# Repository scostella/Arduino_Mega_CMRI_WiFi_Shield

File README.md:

# Arduino Mega CMRI WiFi Shield

The **Arduino Mega CMRI WiFi Shield** is a custom expansion board designed to **plug directly into an Arduino Mega 2560**, organizing digital and analog I/O into structured panel‑based connectors while integrating an **ESP8266 ESP‑01** module to provide WiFi connectivity.

When used with the **Arduino CMRI Library**, this shield allows the Arduino Mega to emulate a **CMRI node** supporting both input and output operations over a network connection.

NOTE: It is highly recommended that your JMRI workstation uses a wired connection to the network.  
---

## Overview

The Arduino Mega CMRI WiFi Shield serves as the central interface between an Arduino Mega 2560, auxiliary I/O modules, and a WiFi network. The shield groups Arduino pins into standardized connectors for clean wiring and expansion while enabling wireless CMRI communication via an onboard ESP8266 ESP‑01.

This design is intended for modular CMRI systems where distributed I/O and network connectivity are required.

---

## Key Characteristics

- Plugs directly into an **Arduino Mega 2560**
- Groups digital and analog I/O into **16 sets of 4 pins**
- Compatible with the **Arduino CMRI Library**
- Supports both CMRI **input and output** operations
- Integrated **ESP8266 ESP‑01** socket for WiFi connectivity
- Designed to interface with auxiliary modules in this series
- Passive signal routing (no onboard I/O drivers)

---

## Assembled Board

The image above shows the rendered Arduino Mega CMRI WiFi Shield PCB as it plugs directly into an Arduino Mega 2560.

---

## Board Layout and Function

### Panel Header Grid

Just offset to the **left of the center of the board** is a **4 × 4 grid of 4‑pin headers**.

- Each 4‑pin header represents a **designated panel** in the Arduino Mega CMRI WiFi sketch
- Together, these headers group Arduino digital and analog pins into **16 panel connections**
- The pin groupings map directly to CMRI node definitions in software

This layout is designed to integrate cleanly with the auxiliary modules developed for this system, including those listed in the **Reference Projects** section. The standardized grouping simplifies wiring and ensures consistent mapping between hardware modules and CMRI configuration.

---

### Power Input

On the **left side of the board** is a **single 3‑pin header** supplying:

- **12 V**
- **5 V**
- **Ground**

This header provides power to both the Arduino Mega and the shield, allowing a single power entry point for the CMRI node.

---

### ESP8266 WiFi Integration

The shield includes a **single 2 × 4 socket** for an **ESP8266 ESP‑01** module.

- The ESP‑01 is installed **after programming**
- Once installed, it enables WiFi connectivity for the CMRI node
- Communication between the Arduino Mega and ESP8266 is handled entirely in firmware

This configuration allows the Arduino Mega to communicate with **JMRI or other network‑based CMRI control systems** over WiFi.

---

### Status Indicators

The board includes **two onboard LEDs**:

- **Power LED**  
  Indicates that the Arduino Mega and shield are powered

- **CMRI Connection LED**  
  Indicates when **JMRI or another network‑based CMRI control system** is connected to the emulated CMRI node

These LEDs provide immediate visual feedback on system power and network status.

---

## Intended Use

This shield is well suited for:

- CMRI‑based model railroad layouts
- Distributed CMRI I/O nodes
- Control panels and indicators
- Integration with auxiliary CMRI modules
- WiFi‑enabled CMRI systems using JMRI or similar software

---

## Limited Liability and Disclaimer

This project is provided as an **open‑source hardware design** and is offered **as‑is**, without warranty of any kind.

By using this design, documentation, or any assembled hardware provided by the author, you agree to the following:

- You assume **all responsibility** for proper electrical design, wiring, installation, and use
- The author makes **no guarantees** regarding suitability for any specific application
- The author shall not be held liable for:
  - Damage to equipment
  - Electrical failures
  - Personal injury
  - Property damage
  - Losses resulting from improper use, installation, or modification

Use of this project or any associated hardware constitutes acceptance of these terms.

---

## Availability and Purchase

Fully **assembled and tested** Arduino Mega CMRI WiFi Shield boards are available.

- **Price:** $35 USD per board  
- **Shipping:** Additional, based on destination  
- **Contact:**  
  📧 scostella@seancostella.com  

Please contact the author for current availability, lead times, and shipping details.

---

## Reference Projects

This project integrates with the Arduino CMRI ecosystem. The following projects provide related hardware, firmware, and configuration support:

- **Arduino Mega CMRI WiFi**  
  Arduino sketch for Mega 2560 to operate as CMRI Node with an ESP8266-ESP01 providing WiFi connectivity.
  https://github.com/scostella/Arduino_Mega_CMRI_WiFi

- **ESP8266 WiFi Setup Utility**  
  ESP sketch to program the ESP8266-ESP01 to work with the Arduino Mega 2560 and connection configuration for your WiFi network.
  https://github.com/scostella/ESP8266WiFiSetup

- **KiCad Custom Library**  
  Library containing all project parts in all designs.
  https://github.com/scostella/KiCadLibrary

- **Arduino Mega CMRI WiFi Shield**  
  KiCad design for a shield for the Arduino Mega 2560 facilitating easy integration with the ESP8266-ESP01 and the CMRI modules listed below.
  https://github.com/scostella/Arduino_Mega_CMRI_WiFi_Shield

- **Arduino Accessory Controller**  
  KiCad design for a board to control accessories up to 1 amp.
  https://github.com/scostella/Arduino-Accessory-Controller

- **Arduino IR Sensor Module - 8 Port**  
  KiCad design for a board to use TCRT5000 IR module to sense object presence which can also be used in the Arduino Mega CMRI WiFi module to group sensors to create virtual block detection.
  https://github.com/scostella/Arduino_IR_Sensor_Module_-_8_Port

- **Arduino Tortoise Controller with Feedback - 8 Port**  
  KiCad design for a board to control Circuitron Tortoise Slow Motion Switch machines and provide feedback on switch position either controlled internally by the voltage applied to the tortoise or an external signal.
  https://github.com/scostella/Arduino_Tortoise_Controller_with_Feedback_-_8_Port

- **Arduino Light Controller**  
  KiCad design for a board to control low amperage lighting and other loads (<10ma) using the Arduino's 5V source.
  https://github.com/scostella/Arduino-Light-Controller

These projects may be used together to form a complete CMRI‑controlled lighting and I/O system.

---

## Repository Contents

```text
/
├── 3V3VoltageRegulator.kicad_sch               # 3.3V Regulated Power Module
├── Arduino Mega CMRI WiFi Shield.jpg           # Rendered image of assembled board
├── Arduino Mega CMRI WiFi Shield.kicad_pcb     # KiCad PCB Layout
├── Arduino Mega CMRI WiFi Shield.kicad_prl     # KiCad Project Settings
├── Arduino Mega CMRI WiFi Shield.kicad_pro     # KiCad Project
├── Arduino Mega CMRI WiFi Shield.kicad_sch     # KiCad Schematic
├── ArduinoReset.kicad_sch                      # Arduino Reset module
├── ESP8266ESP01WiFi.kicad_sch                  # ESP8266ESP01WiFi module
├── LogicLevelShifter.kicad_sch                 # 5V-3.3V Logic Level Shift module
└── README.md

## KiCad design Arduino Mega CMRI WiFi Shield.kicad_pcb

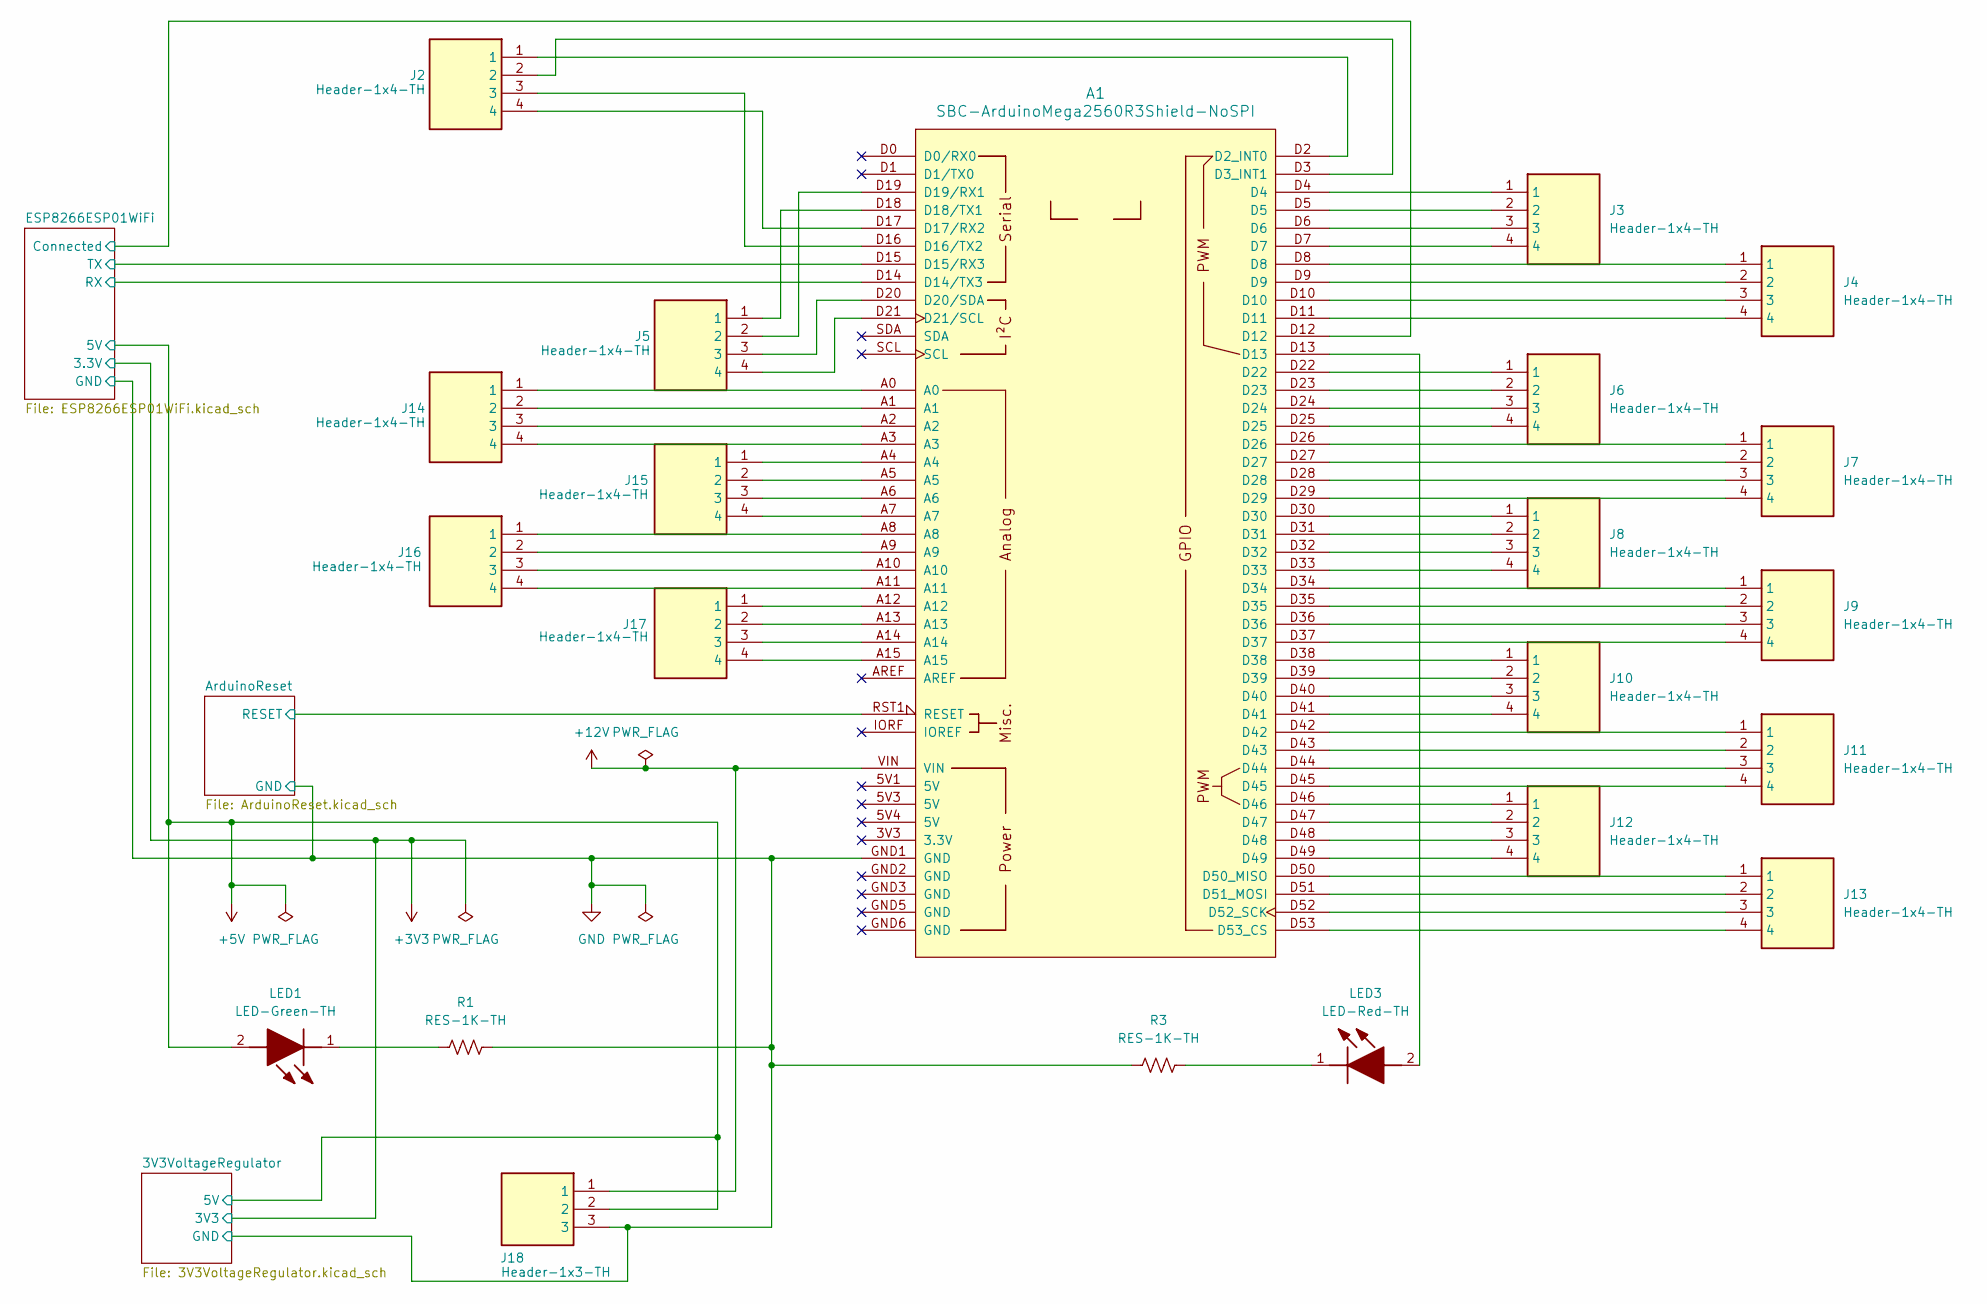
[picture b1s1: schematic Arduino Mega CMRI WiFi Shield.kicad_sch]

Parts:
A1: SBC-ArduinoMega2560R3Shield-NoSPI
J2, J3, J4, J5, J6, J7, J8, J9, J10, J11, J12, J13, J14, J15, J16, J17: Header-1x4-TH; 710-61300411121; Mouser Part Number 710-61300411121
J18: Header-1x3-TH; 710-61300311121; Mouser Part Number 710-61300311121
LED1: LED-Green-TH; 604-WP7113GD; Mouser Part Number 604-WP7113GD
LED3: LED-Red-TH; 604-WP7113ID; Mouser Part Number 604-WP7113ID
R1, R3: RES-1K-TH; R_Axial_DIN0204_L3.6mm_D1.6mm_P7.62mm_Horizontal; Mouser Part Number N/A

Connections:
+5V: J18.2, LED1.2 (A); also elsewhere on the board
+12V: A1.VIN, J18.1
/ArduinoReset/RESET: A1.RST1 (RESET); also elsewhere on the board
/ESP8266ESP01WiFi/Connected: A1.D12; also elsewhere on the board
/ESP8266ESP01WiFi/RX: A1.D14 (D14/TX3); also elsewhere on the board
/ESP8266ESP01WiFi/TX: A1.D15 (D15/RX3); also elsewhere on the board
GND: A1.GND1 (GND), J18.3, R1.2, R3.1; also elsewhere on the board
unnamed: A1.D2 (D2_INT0), J2.1
unnamed: A1.D3 (D3_INT1), J2.2
unnamed: A1.D16 (D16/TX2), J2.3
unnamed: A1.D17 (D17/RX2), J2.4
unnamed: A1.D18 (D18/TX1), J5.1
unnamed: A1.D19 (D19/RX1), J5.2
unnamed: A1.D20 (D20/SDA), J5.3
unnamed: A1.D21 (D21/SCL), J5.4
unnamed: A1.D50 (D50_MISO), J13.1
unnamed: A1.D51 (D51_MOSI), J13.2
unnamed: A1.D52 (D52_SCK), J13.3
unnamed: A1.D53 (D53_CS), J13.4
unnamed: A1.A0, J14.1
unnamed: A1.A1, J14.2
unnamed: A1.A2, J14.3
unnamed: A1.A3, J14.4
unnamed: A1.A4, J15.1
unnamed: A1.A5, J15.2
unnamed: A1.A6, J15.3
unnamed: A1.A7, J15.4
unnamed: A1.A8, J16.1
unnamed: A1.A9, J16.2
unnamed: A1.A10, J16.3
unnamed: A1.A11, J16.4
unnamed: A1.A12, J17.1
unnamed: A1.A13, J17.2
unnamed: A1.A14, J17.3
unnamed: A1.A15, J17.4
unnamed: A1.D4, J3.1
unnamed: A1.D5, J3.2
unnamed: A1.D6, J3.3
unnamed: A1.D7, J3.4
unnamed: A1.D8, J4.1
unnamed: A1.D9, J4.2
unnamed: A1.D10, J4.3
unnamed: A1.D11, J4.4
unnamed: A1.D22, J6.1
unnamed: A1.D23, J6.2
unnamed: A1.D24, J6.3
unnamed: A1.D25, J6.4
unnamed: A1.D26, J7.1
unnamed: A1.D27, J7.2
unnamed: A1.D28, J7.3
unnamed: A1.D29, J7.4
unnamed: A1.D30, J8.1
unnamed: A1.D31, J8.2
unnamed: A1.D32, J8.3
unnamed: A1.D33, J8.4
unnamed: A1.D34, J9.1
unnamed: A1.D35, J9.2
unnamed: A1.D36, J9.3
unnamed: A1.D37, J9.4
unnamed: A1.D38, J10.1
unnamed: A1.D39, J10.2
unnamed: A1.D40, J10.3
unnamed: A1.D41, J10.4
unnamed: A1.D42, J11.1
unnamed: A1.D43, J11.2
unnamed: A1.D44, J11.3
unnamed: A1.D45, J11.4
unnamed: A1.D46, J12.1
unnamed: A1.D47, J12.2
unnamed: A1.D48, J12.3
unnamed: A1.D49, J12.4
unnamed: LED1.1 (K), R1.1
unnamed: A1.D13, LED3.2 (A)
unnamed: LED3.1 (K), R3.2

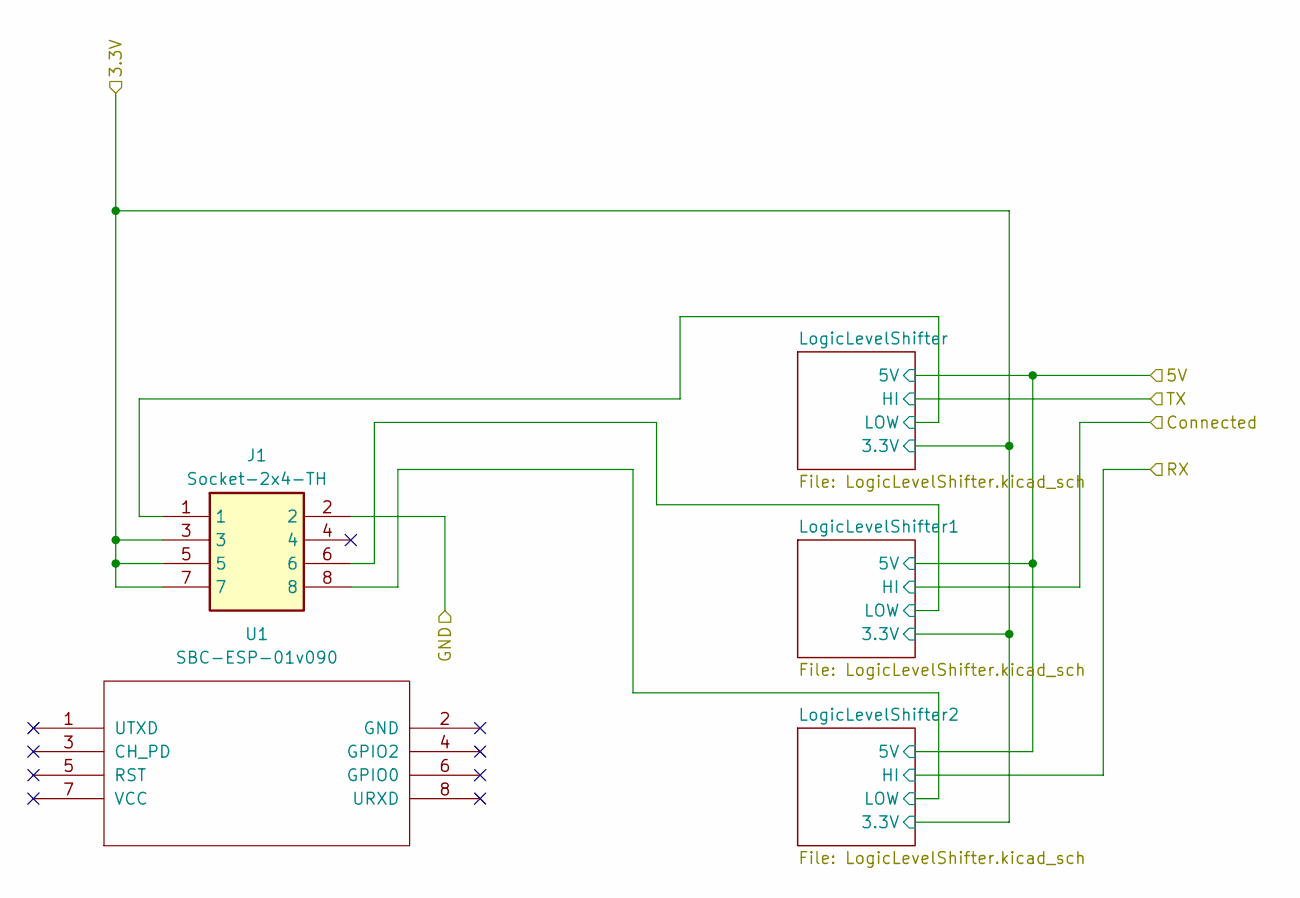
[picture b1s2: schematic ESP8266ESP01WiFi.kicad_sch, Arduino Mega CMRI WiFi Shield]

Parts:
J1: Socket-2x4-TH; 855-M20-7830446; Mouser Part Number 855-M20-7830446
U1: SBC-ESP-01v090; SBC-ESP8266ESP-01

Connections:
+3V3: J1.3, J1.5, J1.7; also elsewhere on the board
/ESP8266ESP01WiFi/LogicLevelShifter1/LOW: J1.6; also elsewhere on the board
/ESP8266ESP01WiFi/LogicLevelShifter2/LOW: J1.8; also elsewhere on the board
/ESP8266ESP01WiFi/LogicLevelShifter/LOW: J1.1; also elsewhere on the board
GND: J1.2; also elsewhere on the board

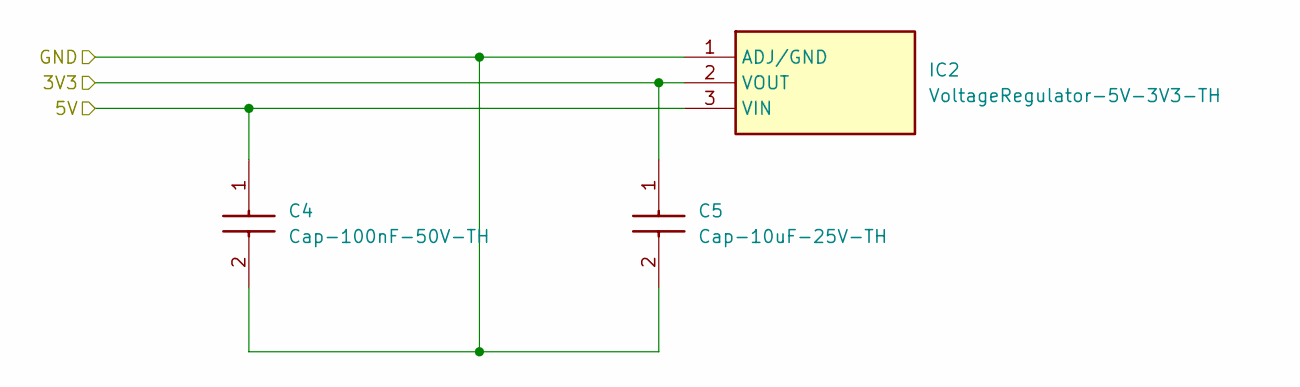
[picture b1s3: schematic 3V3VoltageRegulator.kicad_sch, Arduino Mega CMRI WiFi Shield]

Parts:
C4: Cap-100nF-50V-TH; 80-C315C104M5U; Mouser Part Number 80-C315C104M5U
C5: Cap-10uF-25V-TH; 810-FG16X7R1E106KRT6; Mouser Part Number 810-FG14X7R1A106KRT6
IC2: VoltageRegulator-5V-3V3-TH; 511-LD1117V33C; Mouser Part Number 511-LD1117V33C

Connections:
+3V3: C5.1, IC2.2 (VOUT); also elsewhere on the board
+5V: C4.1, IC2.3 (VIN); also elsewhere on the board
GND: C4.2, C5.2, IC2.1 (ADJ/GND); also elsewhere on the board

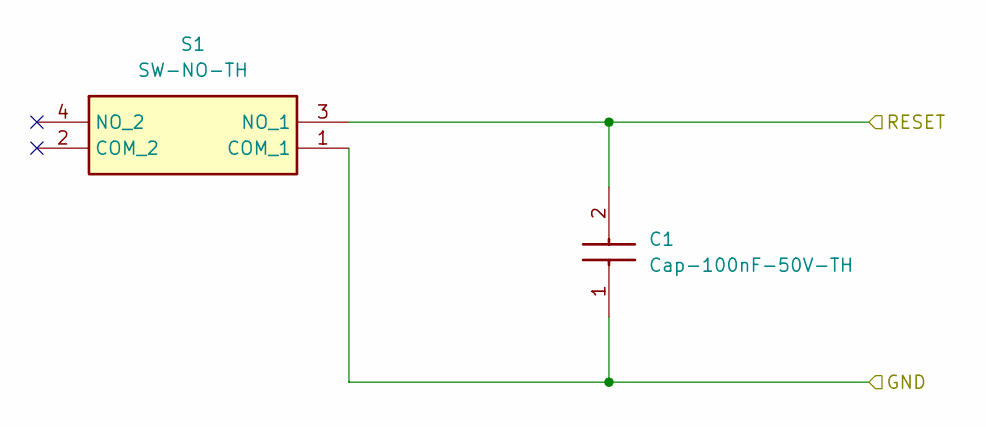
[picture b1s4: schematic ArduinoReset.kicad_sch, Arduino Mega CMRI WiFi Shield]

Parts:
C1: Cap-100nF-50V-TH; 80-C315C104M5U; Mouser Part Number 80-C315C104M5U
S1: SW-NO-TH; 653-B3F-1006; Mouser Part Number 653-B3F-1006

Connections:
/ArduinoReset/RESET: C1.2, S1.3 (NO_1); also elsewhere on the board
GND: C1.1, S1.1 (COM_1); also elsewhere on the board

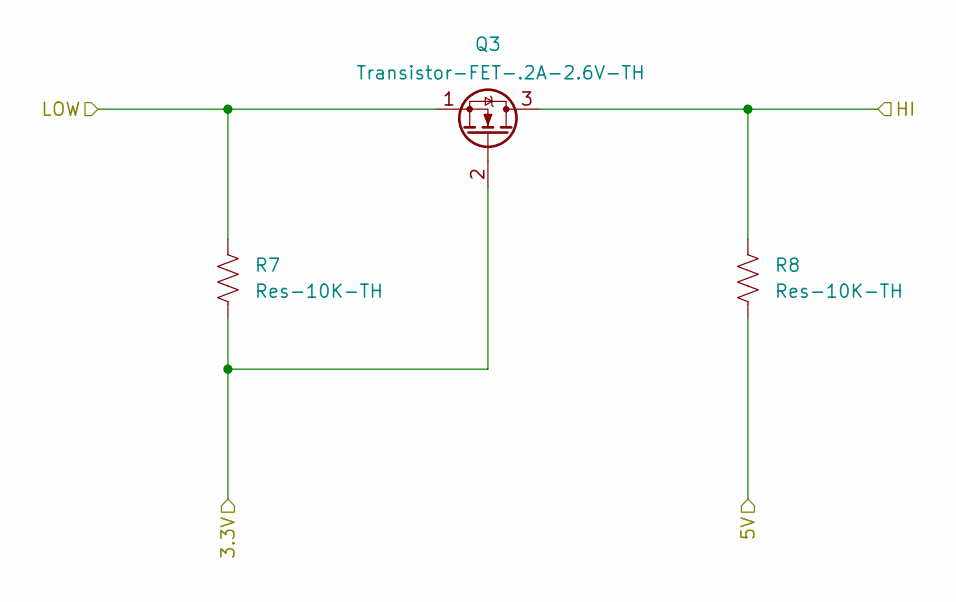
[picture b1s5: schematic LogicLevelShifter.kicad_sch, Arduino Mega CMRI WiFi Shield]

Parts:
Q3: Transistor-FET-.2A-2.6V-TH; 512-2N7000BU; Manufacturer Part Number 2N7000BU
R7, R8: Res-10K-TH; R_Axial_DIN0204_L3.6mm_D1.6mm_P7.62mm_Horizontal; Manufacturer_Part_Number CFR-25JB-52-10K

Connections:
+3V3: Q3.2 (G), R7.2; also elsewhere on the board
+5V: R8.2; also elsewhere on the board
/ESP8266ESP01WiFi/LogicLevelShifter/LOW: Q3.1 (S), R7.1; also elsewhere on the board
/ESP8266ESP01WiFi/TX: Q3.3 (D), R8.1; also elsewhere on the board

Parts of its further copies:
Q1, Q2: Transistor-FET-.2A-2.6V-TH; 512-2N7000BU; Manufacturer Part Number 2N7000BU
R2, R4, R5, R6: Res-10K-TH; R_Axial_DIN0204_L3.6mm_D1.6mm_P7.62mm_Horizontal; Manufacturer_Part_Number CFR-25JB-52-10K

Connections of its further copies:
+3V3: Q1.2 (G), Q2.2 (G), R2.2, R5.2; also elsewhere on the board
+5V: R4.2, R6.2; also elsewhere on the board
/ESP8266ESP01WiFi/Connected: Q1.3 (D), R4.1; also elsewhere on the board
/ESP8266ESP01WiFi/LogicLevelShifter1/LOW: Q1.1 (S), R2.1; also elsewhere on the board
/ESP8266ESP01WiFi/LogicLevelShifter2/LOW: Q2.1 (S), R5.1; also elsewhere on the board
/ESP8266ESP01WiFi/RX: Q2.3 (D), R6.1; also elsewhere on the board

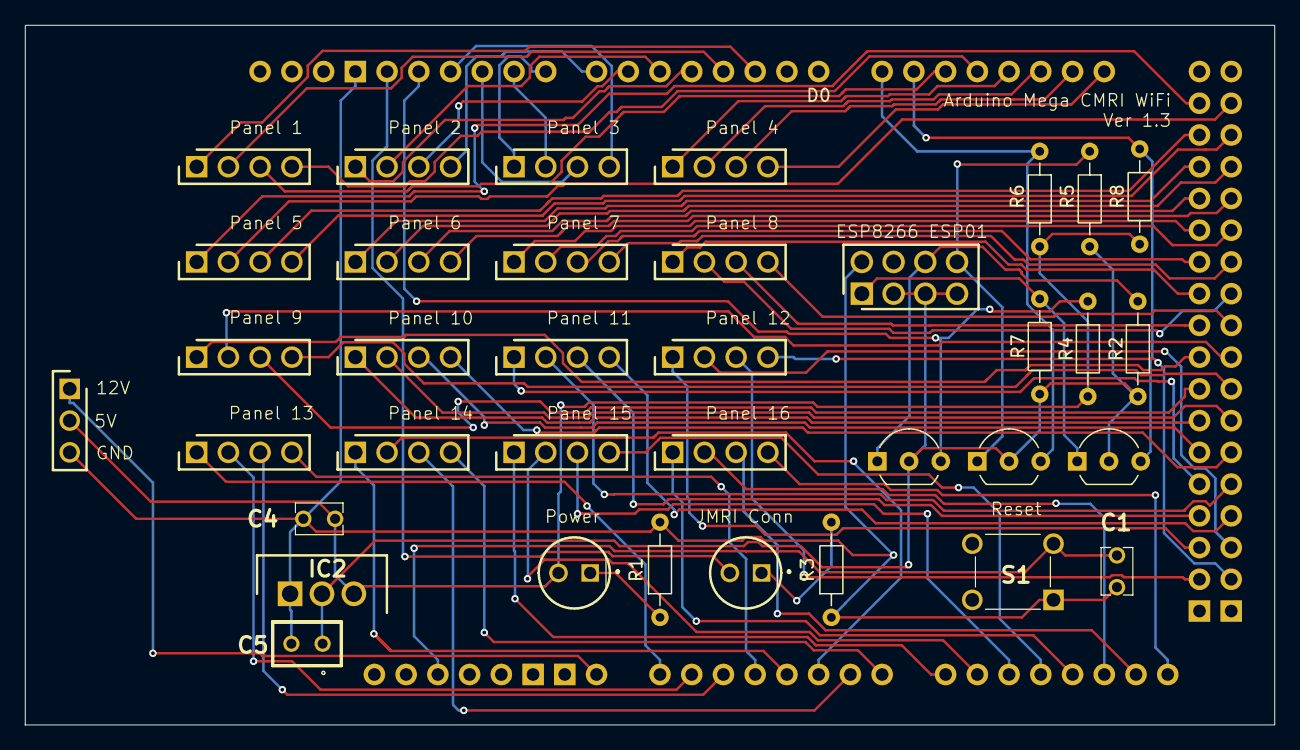
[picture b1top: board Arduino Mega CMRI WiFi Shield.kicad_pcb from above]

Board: 2 copper layers, 100.0 x 56.0 mm, 37 parts (0 on the bottom side), 78 nets.

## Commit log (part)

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2026-01-24 Initial design.
2026-01-24 Created a .gitignore file to exclude backups from the repo.
2026-01-25 Fixed silkscreen issue when 5V was added to power input header. Updated board title version to 1.0B.
2026-01-30 Updated .gitignore to ignore the bom directory.
2026-01-31 Swapped components for those in custom library, updated labelling on PCB.
2026-01-31 Updated sheets with version and date, relaid all traces on PCB.
2026-01-31 Created README.md.
2026-02-10 Added Logic Level Shifter based on 2N7000.
2026-02-10 Added appropriate logic level shifter based on 2N7000 design.
2026-02-10 Updated PCB for the new logic level module.
2026-02-10 Updates look good, promoted to v1.2.
2026-02-10 Re-added labels for resistors to logic level shifter.
2026-02-14 Refreshed PCB to get corrected 3D models to generate the rendered board assembly.
2026-02-14 Rebuil of README.md based on new standard and additional detail.
2026-02-14 Corrected embedded image link.
2026-02-14 Corrected reference to board purchase.
2026-02-14 Corrected indenting for element in Repository Content index.
2026-02-15 Updated README.md with all reference projects.
2026-02-15 Adjusted verbiage on Reference Projects.
2026-02-15 Added KiCad Custom Library to project references.
2026-02-25 Swapped the RX and TX pins between the arduino and the ESP8266-ESP01 that was discovered on prototype board v1.2
2026-03-28 Updated version to 1.3 to reduce confusion from issue where Rx and TX needed swapped.
2026-03-28 Generated new Gerber files for board production.
